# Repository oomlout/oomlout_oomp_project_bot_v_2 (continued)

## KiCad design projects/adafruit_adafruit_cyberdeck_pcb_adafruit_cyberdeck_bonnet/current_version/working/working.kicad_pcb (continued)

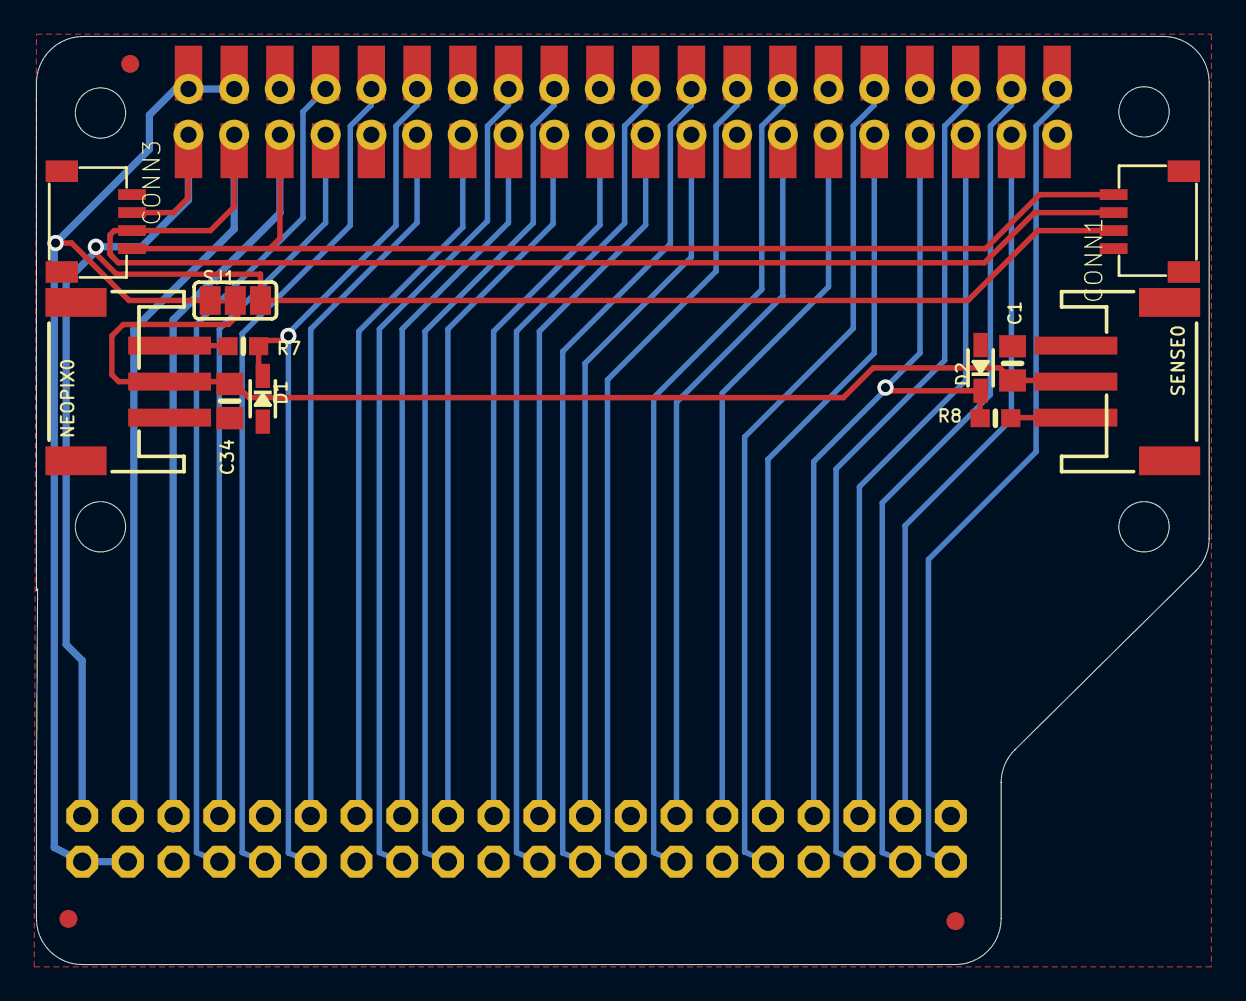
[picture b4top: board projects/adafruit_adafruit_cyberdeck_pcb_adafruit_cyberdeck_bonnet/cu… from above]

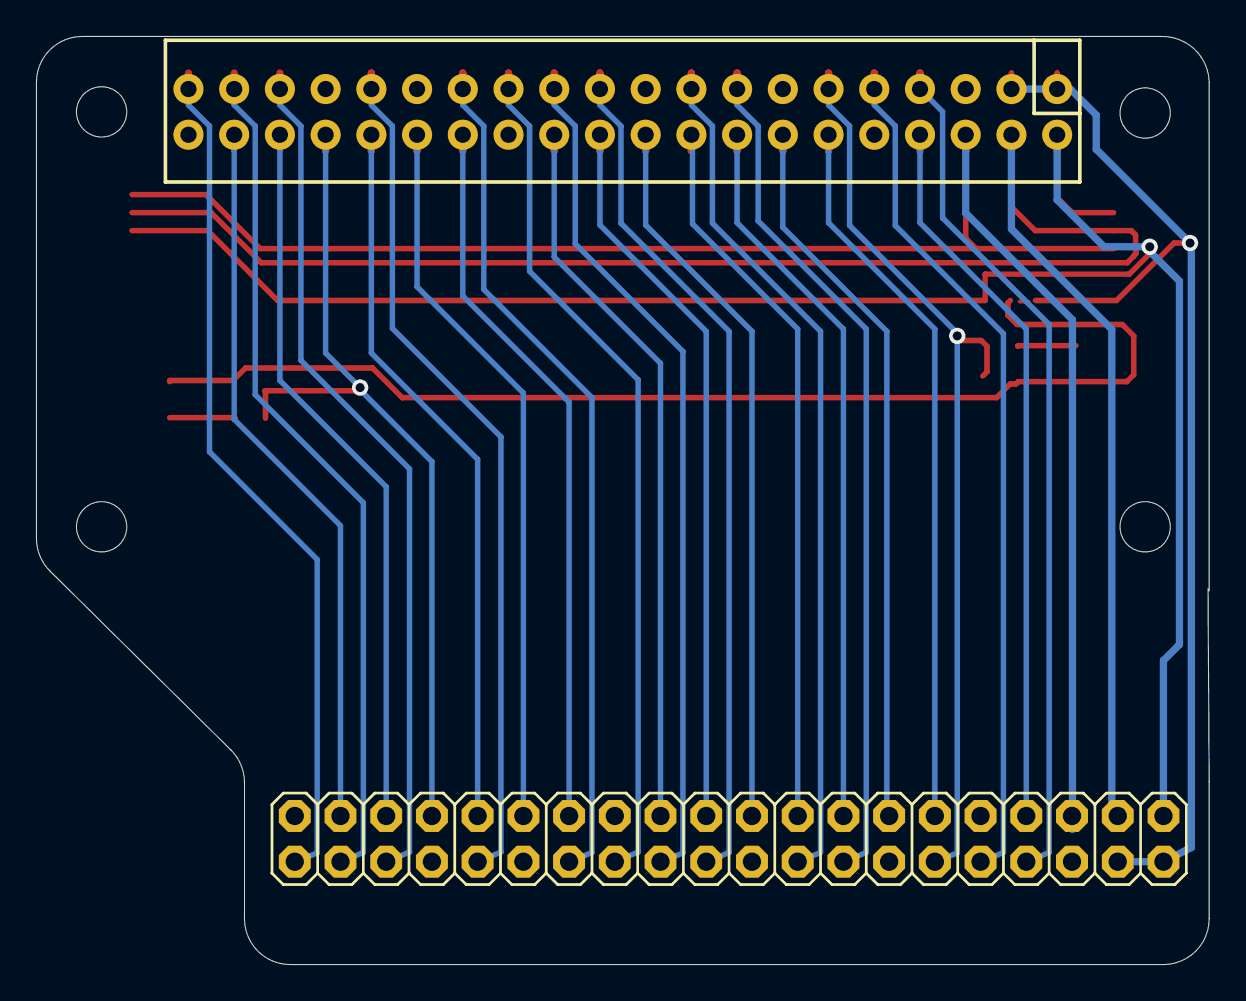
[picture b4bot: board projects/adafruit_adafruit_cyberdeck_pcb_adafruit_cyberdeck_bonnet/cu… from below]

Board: 2 copper layers, 65.2 x 51.6 mm, 22 parts (2 on the bottom side), 35 nets.

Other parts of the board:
@HOLE0, @HOLE1, @HOLE2, @HOLE3: (no value)
U$1: CYBERDECK_BONNET_BOT
U$2: CYBERDECK_BONNET_TOP

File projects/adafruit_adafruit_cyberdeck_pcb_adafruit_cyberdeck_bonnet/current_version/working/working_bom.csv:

"Id";"Designator";"Footprint";"Quantity";"Designation";"Supplier and ref";
1;"FID3,FID2,FID1";"FIDUCIAL_1MM";3;"FIDUCIAL_1MM";;;
2;"CONN3,CONN1";"JST_SH4";2;"STEMMA_I2C_QT";;;
3;"R7,R8";"0603-NO";2;"1K";;;
4;"C1,C34";"0805-NO";2;"10uF";;;
5;"@HOLE0,@HOLE2,@HOLE1,@HOLE3";"";4;"";;;
6;"NEOPIX0,SENSE0";"JSTPH3";2;"JST PH 3";;;
7;"U$2";"CYBERDECK_BONNET_TOP";1;"";;;
8;"RPI2";"RASPI_2X20_THMSMT_TOP";1;"RASPBERRYPI_BPLUS_2X20_THMSMT_TOP";;;
9;"D2,D1";"SOD-323";2;"3.6V";;;
10;"SJ1";"SOLDERJUMPER_2WAY_OPEN_NOPASTE";1;"";;;
11;"RPI1";"2X20";1;"RASPBERRYPI_BPLUS_IDC";;;
12;"U$1";"CYBERDECK_BONNET_BOT";1;"";;;

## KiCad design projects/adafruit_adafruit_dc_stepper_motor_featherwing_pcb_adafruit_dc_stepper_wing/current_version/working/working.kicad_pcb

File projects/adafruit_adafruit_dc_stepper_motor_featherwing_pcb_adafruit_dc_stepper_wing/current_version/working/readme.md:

# adafruit_dc_stepper_motor_featherwing_pcb
 
## summary 
* id: adafruit_adafruit_dc_stepper_motor_featherwing_pcb_adafruit_dc_stepper_wing
* user: adafruit
* name: adafruit_dc_stepper_motor_featherwing_pcb
* board: adafruit_dc_stepper_wing
* repo: https://github.com/adafruit/Adafruit-DC-Stepper-Motor-FeatherWing-PCB

* src_file_repo_sch: 
* src_file_repo_sch_link: https://github.com/adafruit/Adafruit-DC-Stepper-Motor-FeatherWing-PCB/tree/master/
* full details link: https://github.com/oomlout/oomlout_oomp_project_bot_v_2/tree/main/projects/adafruit_adafruit_dc_stepper_motor_featherwing_pcb_adafruit_dc_stepper_wing/current_version/working  

## schematic  
  
[schematic (pdf)](working_schematic.pdf) 

## pcb  

[board (pdf)](working.pdf)  

## working_bom
| Id | Designator | Footprint | Quantity | Designation | Supplier and ref |  | None | 
| --- | --- | --- | --- | --- | --- | --- | --- | 
| 1 | R9,R10 | RESPACK_4X0603 | 2 | 10K |  |  | [''] | 
| 2 | C2 | 0805-NO | 1 | 0.1uF |  |  | [''] | 
| 3 | U$4,U$3 | FIDUCIAL_1MM | 2 | FIDUCIAL" |  |  | [''] | 
| 4 | C6,C10 | 0805-NO | 2 | 10uF |  |  | [''] | 
| 5 | U$2 | SYMBOL_MINUS | 1 |  |  |  | [''] | 
| 6 | R4 | 0805-NO | 1 | 1K |  |  | [''] | 
| 7 | X1,X4,X6,X2 | TERMBLOCK_1X2-3.5MM | 4 |  |  |  | [''] | 
| 8 | MS1 | FEATHERWING | 1 | FEATHERWING |  |  | [''] | 
| 9 | LED1 | CHIPLED_0805_NOOUTLINE | 1 | Green |  |  | [''] | 
| 10 | SW1 | BTN_KMR2_4.6X2.8 | 1 |  |  |  | [''] | 
| 11 | MPOWER0 | 1X2-3.5MM | 1 | 1X2-3.5MM |  |  | [''] | 
| 12 | U$5 | ADAFRUIT_3.5MM | 1 |  |  |  | [''] | 
| 13 | U2 | TSSOP28 | 1 | PCA9685 |  |  | [''] | 
| 14 | Q1 | POWERDI3333 | 1 | AON7401 |  |  | [''] | 
| 15 | C5 | PANASONIC_C | 1 | 47uF+/16v |  |  | [''] | 
| 16 | JP1 | 1X12_ROUND | 1 |  |  |  | [''] | 
| 17 | IC3,IC1 | SSOP24 | 2 | TB6612FNG |  |  | [''] | 
| 18 | JP2 | 1X16_ROUND | 1 |  |  |  | [''] | 
| 19 | C4 | PANASONIC_C | 1 | 47uF/16v |  |  | [''] | 
| 20 | U$1 | SYMBOL_PLUS | 1 |  |  |  | [''] | 
| 21 | A0,A1,A4,A3,A2 | SOLDERJUMPER_REFLOW_NOPASTE | 5 |  |  |  | [''] | 
| 22 | U$6 | FEATHERLOGO | 1 |  |  |  | [''] | 
| 23 | U$8 | PCBFEAT-REV-040 | 1 |  |  |  | [''] | 

## bom_schematic
| Ref | Qnty | Value | Cmp name | Footprint | Description | Vendor | DNP | 
| --- | --- | --- | --- | --- | --- | --- | --- | 
| A0, A1, A2, A3, A4 | 5 | SOLDERJUMPERREFLOW_NOPASTE | SOLDERJUMPERREFLOW_NOPASTE | working:SOLDERJUMPER_REFLOW_NOPASTE |  |  |  | 
| C2 | 1 | 0.1uF | CAP_CERAMIC0805-NOOUTLINE | working:0805-NO |  |  |  | 
| C4 | 1 | 47uF/16v | CAP_ELECTROLYTICPANASONIC_C | working:PANASONIC_C |  |  |  | 
| C5 | 1 | 47uF+/16v | CAP_ELECTROLYTICPANASONIC_C | working:PANASONIC_C |  |  |  | 
| C6, C10 | 2 | 10uF | CAP_CERAMIC0805-NOOUTLINE | working:0805-NO |  |  |  | 
| IC1, IC3 | 2 | TB6612FNG | TB6612FNG | working:SSOP24 |  |  |  | 
| JP1 | 1 | HEADER-1X12 | HEADER-1X12 | working:1X12_ROUND |  |  |  | 
| JP2 | 1 | HEADER-1X16ROUND | HEADER-1X16ROUND | working:1X16_ROUND |  |  |  | 
| LED1 | 1 | Green | LED0805_NOOUTLINE | working:CHIPLED_0805_NOOUTLINE |  |  |  | 
| MPOWER0 | 1 | 1X2-3.5MM | 1X2-3.5MM | working:1X2-3.5MM |  |  |  | 
| MS1 | 1 | FEATHERWING | FEATHERWING | working:FEATHERWING |  |  |  | 
| Q1 | 1 | AON7401 | MOSFET-P-POWERDI3333 | working:POWERDI3333 |  |  |  | 
| R4 | 1 | 1K | RESISTOR0805_NOOUTLINE | working:0805-NO |  |  |  | 
| R9, R10 | 2 | 10K | RESISTOR_4PACK | working:RESPACK_4X0603 |  |  |  | 
| SW1 | 1 | SWITCH_TACT_SMT4.6X2.8 | SWITCH_TACT_SMT4.6X2.8 | working:BTN_KMR2_4.6X2.8 |  |  |  | 
| U2 | 1 | PCA9685 | PCA9685 | working:TSSOP28 |  |  |  | 
| U$3, U$4 | 2 | FIDUCIAL"" | FIDUCIAL{dblquote}{dblquote} | working:FIDUCIAL_1MM |  |  |  | 
| X1, X2, X4, X6 | 4 | TERMBLOCK_1X2 | TERMBLOCK_1X2 | working:TERMBLOCK_1X2-3.5MM |  |  |  |

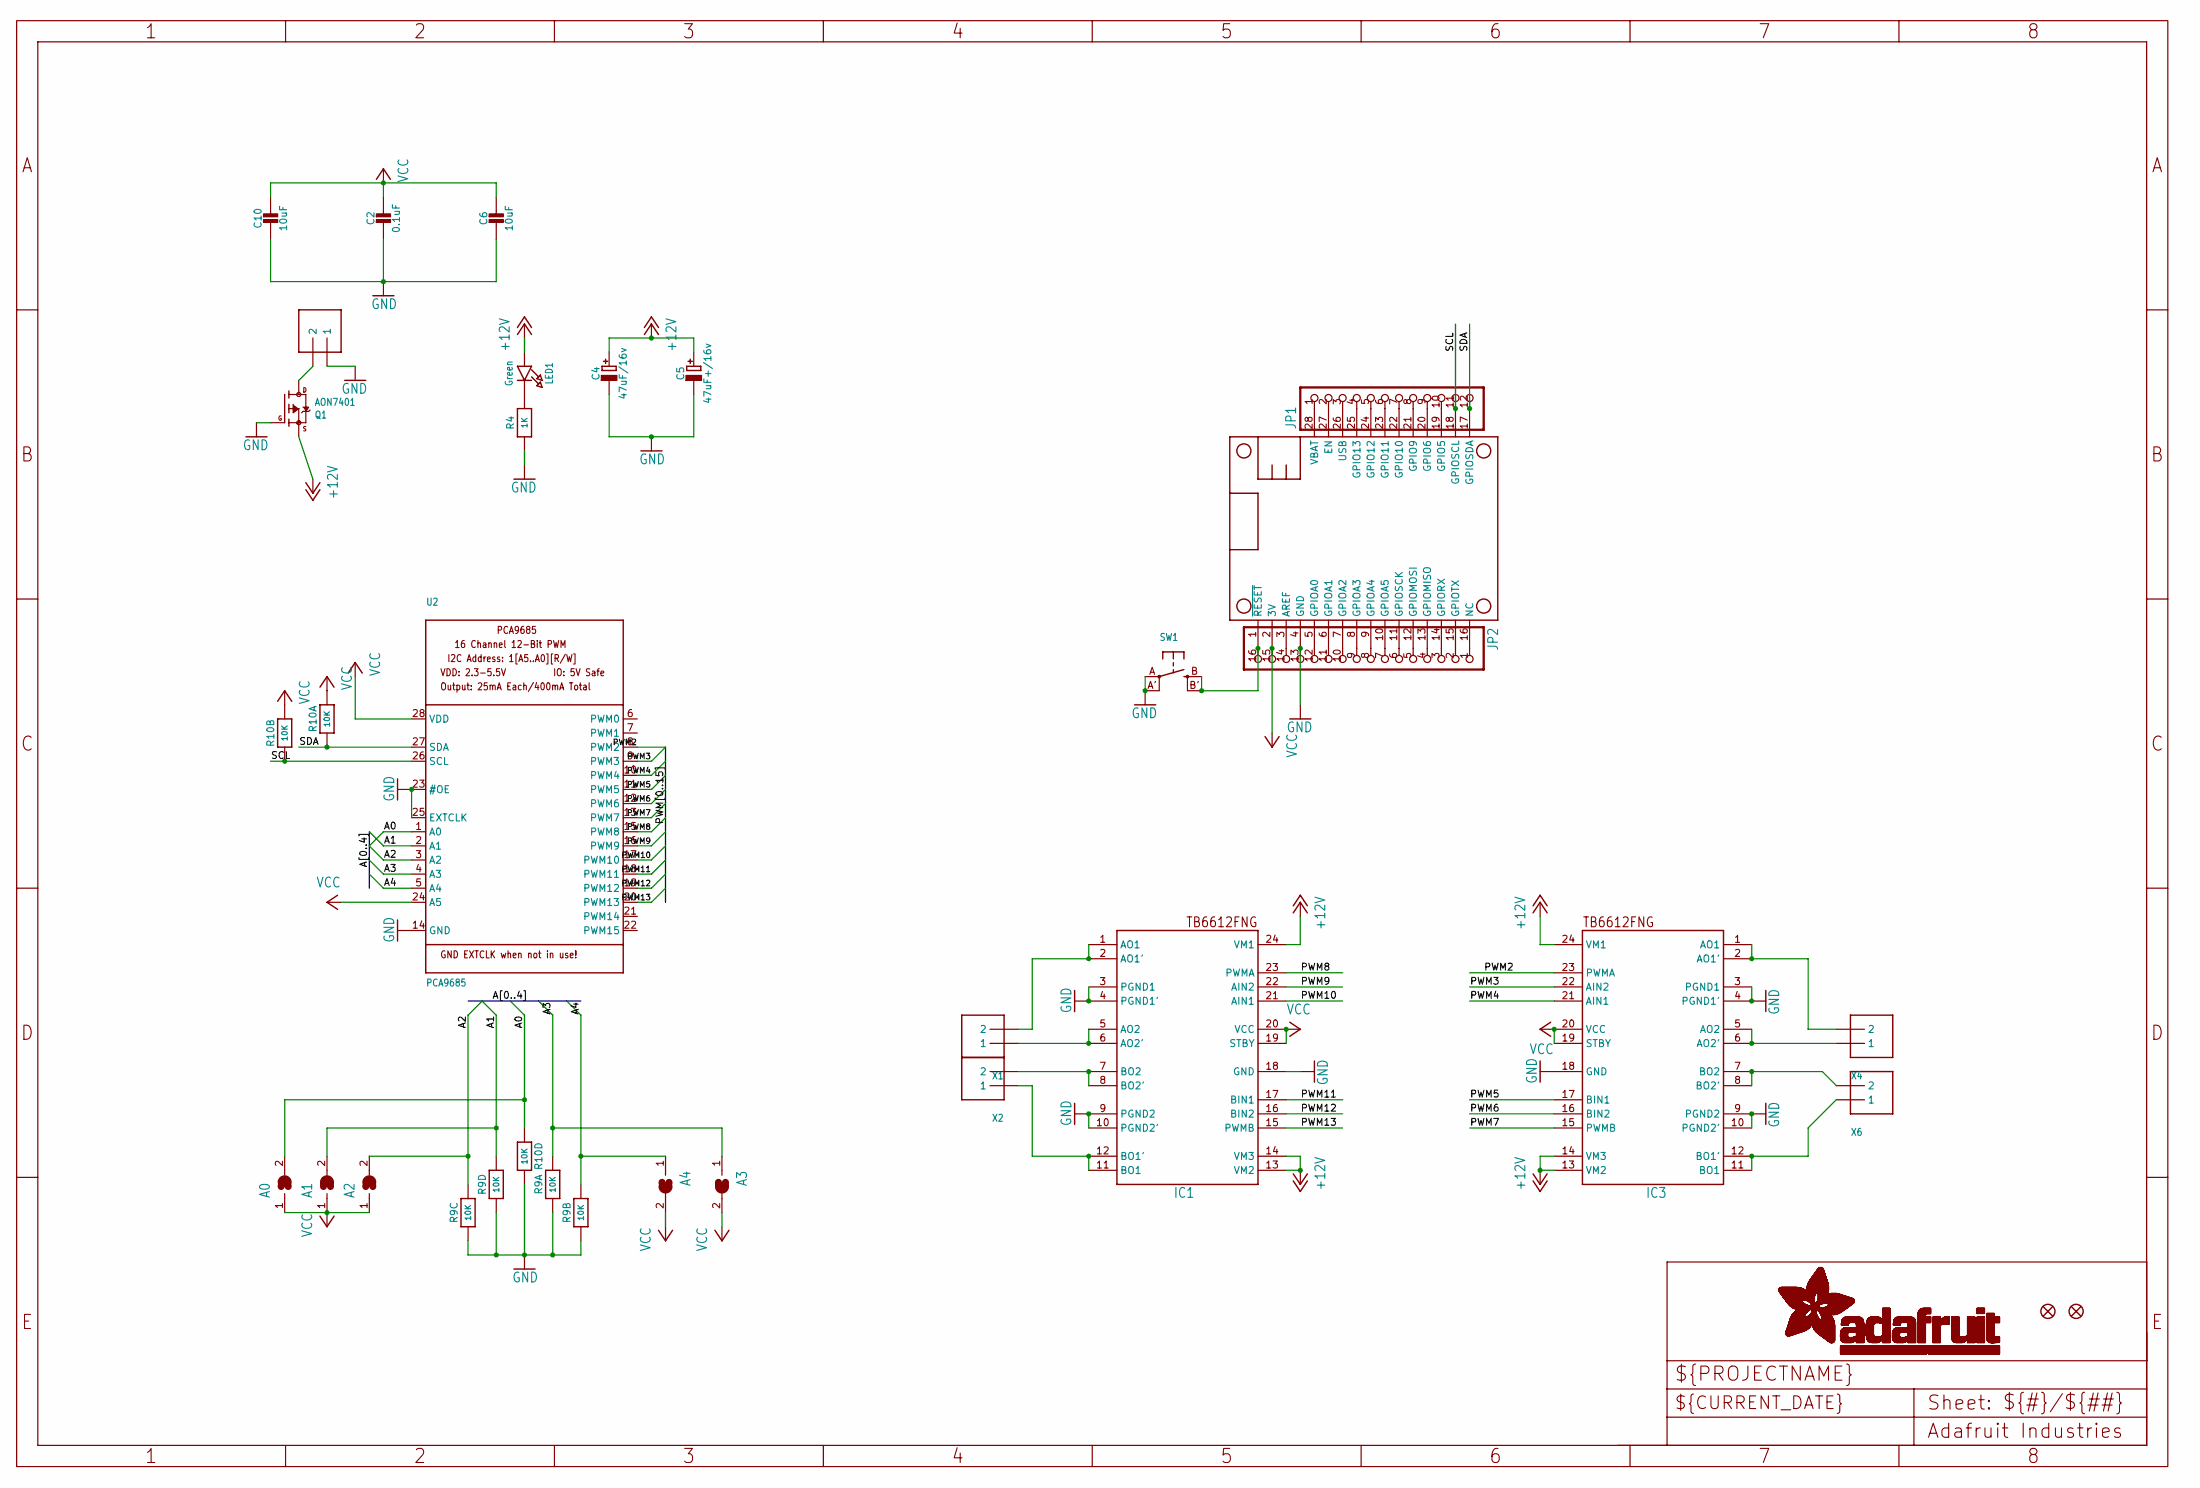
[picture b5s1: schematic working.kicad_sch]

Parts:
A0, A1, A2, A3, A4: SOLDERJUMPERREFLOW_NOPASTE; SOLDERJUMPER_REFLOW_NOPASTE
C2: 0.1uF; 0805-NO
C4: 47uF/16v; PANASONIC_C
C5: 47uF+/16v; PANASONIC_C
C6, C10: 10uF; 0805-NO
IC1, IC3: TB6612FNG; SSOP24
JP1: HEADER-1X12; 1X12_ROUND
JP2: HEADER-1X16ROUND; 1X16_ROUND
LED1: Green; CHIPLED_0805_NOOUTLINE
MPOWER0: 1X2-3.5MM
MS1: FEATHERWING
Q1: AON7401; POWERDI3333
R4: 1K; 0805-NO
R9, R10: 10K; RESPACK_4X0603
SW1: SWITCH_TACT_SMT4.6X2.8; BTN_KMR2_4.6X2.8
U2: PCA9685; TSSOP28
U$3, U$4: FIDUCIAL""; FIDUCIAL_1MM
X1, X2, X4, X6: TERMBLOCK_1X2; TERMBLOCK_1X2-3.5MM

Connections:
+12V: C4.+, C5.+, IC1.13 (VM2), IC1.14 (VM3), IC1.24 (VM1), IC3.13 (VM2), IC3.14 (VM3), IC3.24 (VM1), LED1.A, Q1.1 (S), Q1.2 (S), Q1.3 (S)
A0: A0.2, R10.4 (1), U2.1 (A0)
A1: A1.2, R9.5 (2), U2.2 (A1)
A2: A2.2, R9.6 (2), U2.3 (A2)
A3: A3.1, R9.8 (2), U2.4 (A3)
A4: A4.1, R9.7 (2), U2.5 (A4)
GND: C2.2, C4.-, C5.-, C6.2, C10.2, IC1.3 (PGND1), IC1.4 (PGND1'), IC1.9 (PGND2), IC1.10 (PGND2'), IC1.18 (GND), IC3.3 (PGND1), IC3.4 (PGND1'), IC3.9 (PGND2), IC3.10 (PGND2'), IC3.18 (GND), JP2.13, MPOWER0.1, MS1.4 (GND), Q1.4 (G), R4.1, R9.1, R9.2 (1), R9.3 (1), R9.4 (1), R10.5 (2), SW1.A, SW1.A' (P1), U2.14 (GND), U2.23 (#OE), U2.25 (EXTCLK)
unnamed: JP1.2, MS1.27 (EN)
unnamed: JP1.4, MS1.25 (GPIO13)
unnamed: MPOWER0.2, Q1.5678 (D)
unnamed: IC1.1 (AO1), IC1.2 (AO1'), X1.2
unnamed: JP1.5, MS1.24 (GPIO12)
unnamed: IC1.5 (AO2), IC1.6 (AO2'), X1.1
unnamed: IC1.7 (BO2), IC1.8 (BO2'), X2.2
unnamed: JP1.6, MS1.23 (GPIO11)
unnamed: IC1.11 (BO1), IC1.12 (BO1'), X2.1
unnamed: JP1.7, MS1.22 (GPIO10)
unnamed: JP1.8, MS1.21 (GPIO9)
unnamed: IC3.1 (AO1), IC3.2 (AO1'), X4.2
unnamed: JP1.9, MS1.20 (GPIO6)
unnamed: IC3.5 (AO2), IC3.6 (AO2'), X4.1
unnamed: IC3.7 (BO2), IC3.8 (BO2'), X6.2
unnamed: JP1.10, MS1.19 (GPIO5)
unnamed: IC3.11 (BO1), IC3.12 (BO1'), X6.1
unnamed: JP2.1, MS1.16 (NC)
unnamed: JP2.2, MS1.15 (GPIOTX)
unnamed: JP2.3, MS1.14 (GPIORX)
unnamed: JP2.4, MS1.13 (GPIOMISO)
unnamed: JP2.5, MS1.12 (GPIOMOSI)
unnamed: JP2.6, MS1.11 (GPIOSCK)
unnamed: JP2.7, MS1.10 (GPIOA5)
unnamed: JP2.8, MS1.9 (GPIOA4)
unnamed: JP2.9, MS1.8 (GPIOA3)
unnamed: JP2.10, MS1.7 (GPIOA2)
unnamed: JP2.11, MS1.6 (GPIOA1)
unnamed: JP2.12, MS1.5 (GPIOA0)
unnamed: JP2.14, MS1.3 (AREF)
unnamed: JP2.16, MS1.1 (~RESET), SW1.B (S), SW1.B' (S1)
unnamed: LED1.C, R4.2
PWM2: IC3.23 (PWMA), U2.8 (PWM2)
PWM3: IC3.22 (AIN2), U2.9 (PWM3)
PWM4: IC3.21 (AIN1), U2.10 (PWM4)
PWM5: IC3.17 (BIN1), U2.11 (PWM5)
PWM6: IC3.16 (BIN2), U2.12 (PWM6)
PWM7: IC3.15 (PWMB), U2.13 (PWM7)
PWM8: IC1.23 (PWMA), U2.15 (PWM8)
PWM9: IC1.22 (AIN2), U2.16 (PWM9)
PWM10: IC1.21 (AIN1), U2.17 (PWM10)
PWM11: IC1.17 (BIN1), U2.18 (PWM11)
PWM12: IC1.16 (BIN2), U2.19 (PWM12)
PWM13: IC1.15 (PWMB), U2.20 (PWM13)
SCL: JP1.11, MS1.18 (GPIOSCL), R10.2 (1), U2.26 (SCL)
SDA: JP1.12, MS1.17 (GPIOSDA), R10.1, U2.27 (SDA)
USB: JP1.3, MS1.26 (USB)
VBAT: JP1.1, MS1.28 (VBAT)
VCC: A0.1, A1.1, A2.1, A3.2, A4.2, C2.1, C6.1, C10.1, IC1.19 (STBY), IC1.20 (VCC), IC3.19 (STBY), IC3.20 (VCC), JP2.15, MS1.2 (3V), R10.7 (2), R10.8 (2), U2.24 (A5), U2.28 (VDD)

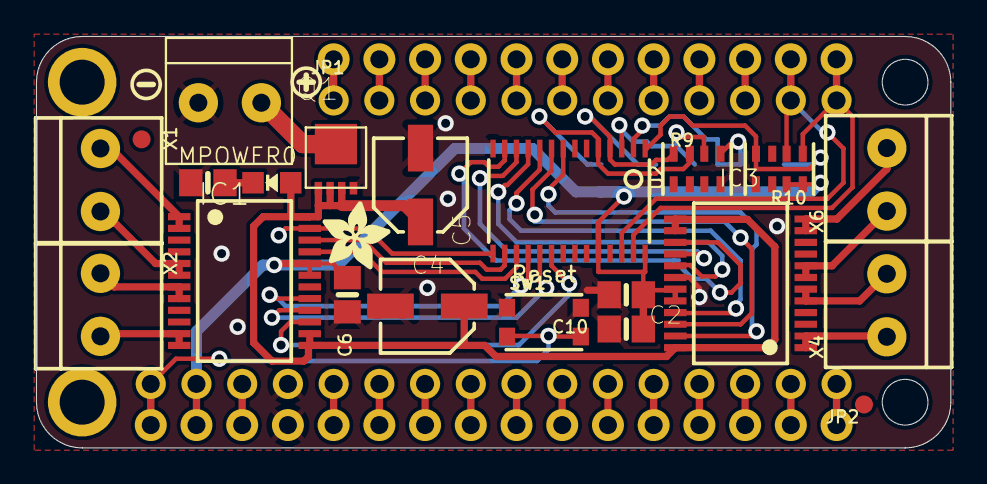
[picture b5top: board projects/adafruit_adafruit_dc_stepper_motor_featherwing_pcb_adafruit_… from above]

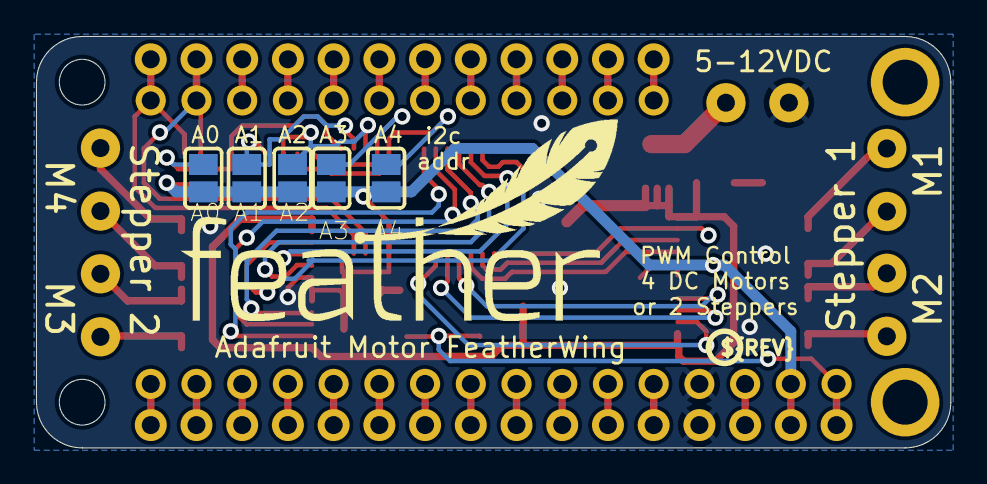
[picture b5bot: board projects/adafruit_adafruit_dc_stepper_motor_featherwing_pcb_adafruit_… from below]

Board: 16 copper layers, 50.8 x 22.9 mm, 34 parts (7 on the bottom side), 56 nets.

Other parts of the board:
U$1: SYMBOL_PLUS
U$2: SYMBOL_MINUS
U$5: ADAFRUIT_3.5MM
U$6: FEATHERLOGO
U$8: PCBFEAT-REV-040

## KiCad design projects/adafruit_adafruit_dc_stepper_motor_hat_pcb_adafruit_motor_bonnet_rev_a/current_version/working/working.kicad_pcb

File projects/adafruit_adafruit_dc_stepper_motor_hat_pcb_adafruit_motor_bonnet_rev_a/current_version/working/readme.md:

# adafruit_dc_stepper_motor_hat_pcb
 
## summary 
* id: adafruit_adafruit_dc_stepper_motor_hat_pcb_adafruit_motor_bonnet_rev_a
* user: adafruit
* name: adafruit_dc_stepper_motor_hat_pcb
* board: adafruit_motor_bonnet_rev_a
* repo: https://github.com/adafruit/Adafruit-DC-Stepper-Motor-HAT-PCB

* src_file_repo_sch: 
* src_file_repo_sch_link: https://github.com/adafruit/Adafruit-DC-Stepper-Motor-HAT-PCB/tree/master/
* full details link: https://github.com/oomlout/oomlout_oomp_project_bot_v_2/tree/main/projects/adafruit_adafruit_dc_stepper_motor_hat_pcb_adafruit_motor_bonnet_rev_a/current_version/working  

## schematic  
  
[schematic (pdf)](working_schematic.pdf) 

## pcb  

[board (pdf)](working.pdf)  

## working_bom
| Id | Designator | Footprint | Quantity | Designation | Supplier and ref |  | None | 
| --- | --- | --- | --- | --- | --- | --- | --- | 
| 1 | MPOWER0 | 1X2-3.5MM | 1 | 1X2-3.5MM |  |  | [''] | 
| 2 | C6,C10 | 0805-NO | 2 | 10uF |  |  | [''] | 
| 3 | Q1 | D-PAK_TO252AA | 1 | AOD417 |  |  | [''] | 
| 4 | U2 | TSSOP28 | 1 | PCA9685 |  |  | [''] | 
| 5 | RPI1 | PI_BONNET_THMSMT | 1 | RASPBERRYPI_BPLUS_BONNET_THMSMT |  |  | [''] | 
| 6 | C5 | PANASONIC_C | 1 | 47uF+/16v |  |  | [''] | 
| 7 | R2 | 0603-NO | 1 | 10K |  |  | [''] | 
| 8 | R7 | 0603-NO | 1 | 1K |  |  | [''] | 
| 9 | C3,C1 | 0603-NO | 2 | 0.1uF |  |  | [''] | 
| 10 | IC1,IC3 | SSOP24 | 2 | TB6612FNG |  |  | [''] | 
| 11 | FID2,FID1,FID3 | FIDUCIAL_1MM | 3 | FIDUCIAL_1MM |  |  | [''] | 
| 12 | LED1 | CHIPLED_0805_NOOUTLINE | 1 | Green |  |  | [''] | 
| 13 | J1,J3 | 1X05-3.5MM | 2 | 1X5 |  |  | [''] | 
| 14 | U$6 | PCBFEAT-REV-040 | 1 |  |  |  | [''] | 
| 15 | JP1 | 1X04_ROUND | 1 |  |  |  | [''] | 
| 16 | C4 | PANASONIC_C | 1 | 47uF/16v |  |  | [''] | 
| 17 | R1 | RESPACK_4X0603 | 1 | 10K |  |  | [''] | 
| 18 | CONN1 | 1X25_ROUND_70MIL | 1 | HEADER-1X25 |  |  | [''] | 
| 19 | U$51 | ADAFRUIT_5MM | 1 |  |  |  | [''] | 
| 20 | A1,A2,A3,A4,A0 | SOLDERJUMPER_REFLOW_NOPASTE | 5 |  |  |  | [''] | 
| 21 | U$8 | ADAFRUIT_TEXT_20MM | 1 |  |  |  | [''] | 

## bom_schematic
| Ref | Qnty | Value | Cmp name | Footprint | Description | Vendor | DNP | 
| --- | --- | --- | --- | --- | --- | --- | --- | 
| A0, A1, A2, A3, A4 | 5 | SOLDERJUMPERREFLOW_NOPASTE | SOLDERJUMPERREFLOW_NOPASTE | working:SOLDERJUMPER_REFLOW_NOPASTE |  |  |  | 
| C1, C3 | 2 | 0.1uF | CAP_CERAMIC0603_NO | working:0603-NO |  |  |  | 
| C4 | 1 | 47uF/16v | CAP_ELECTROLYTICPANASONIC_C | working:PANASONIC_C |  |  |  | 
| C5 | 1 | 47uF+/16v | CAP_ELECTROLYTICPANASONIC_C | working:PANASONIC_C |  |  |  | 
| C6, C10 | 2 | 10uF | CAP_CERAMIC0805-NOOUTLINE | working:0805-NO |  |  |  | 
| CONN1 | 1 | HEADER-1X25 | HEADER-1X25 | working:1X25_ROUND_70MIL |  |  |  | 
| FID1, FID2, FID3 | 3 | FIDUCIAL_1MM | FIDUCIAL_1MM | working:FIDUCIAL_1MM |  |  |  | 
| IC1, IC3 | 2 | TB6612FNG | TB6612FNG | working:SSOP24 |  |  |  | 
| J1, J3 | 2 | 1X5 | 1X5 | working:1X05-3.5MM |  |  |  | 
| JP1 | 1 | HEADER-1X4ROUND | HEADER-1X4ROUND | working:1X04_ROUND |  |  |  | 
| LED1 | 1 | Green | LED0805_NOOUTLINE | working:CHIPLED_0805_NOOUTLINE |  |  |  | 
| MPOWER0 | 1 | 1X2-3.5MM | 1X2-3.5MM | working:1X2-3.5MM |  |  |  | 
| Q1 | 1 | IRF?5305R | IRF?5305R | working:D-PAK_TO252AA |  |  |  | 
| R1 | 1 | 10K | RESISTOR_4PACK | working:RESPACK_4X0603 |  |  |  | 
| R2 | 1 | 10K | RESISTOR_0603_NOOUT | working:0603-NO |  |  |  | 
| R7 | 1 | 1K | RESISTOR_0603_NOOUT | working:0603-NO |  |  |  | 
| RPI1 | 1 | RASPBERRYPI_BPLUS_BONNET_THMSMT | RASPBERRYPI_BPLUS_BONNET_THMSMT | working:PI_BONNET_THMSMT |  |  |  | 
| U2 | 1 | PCA9685 | PCA9685 | working:TSSOP28 |  |  |  |

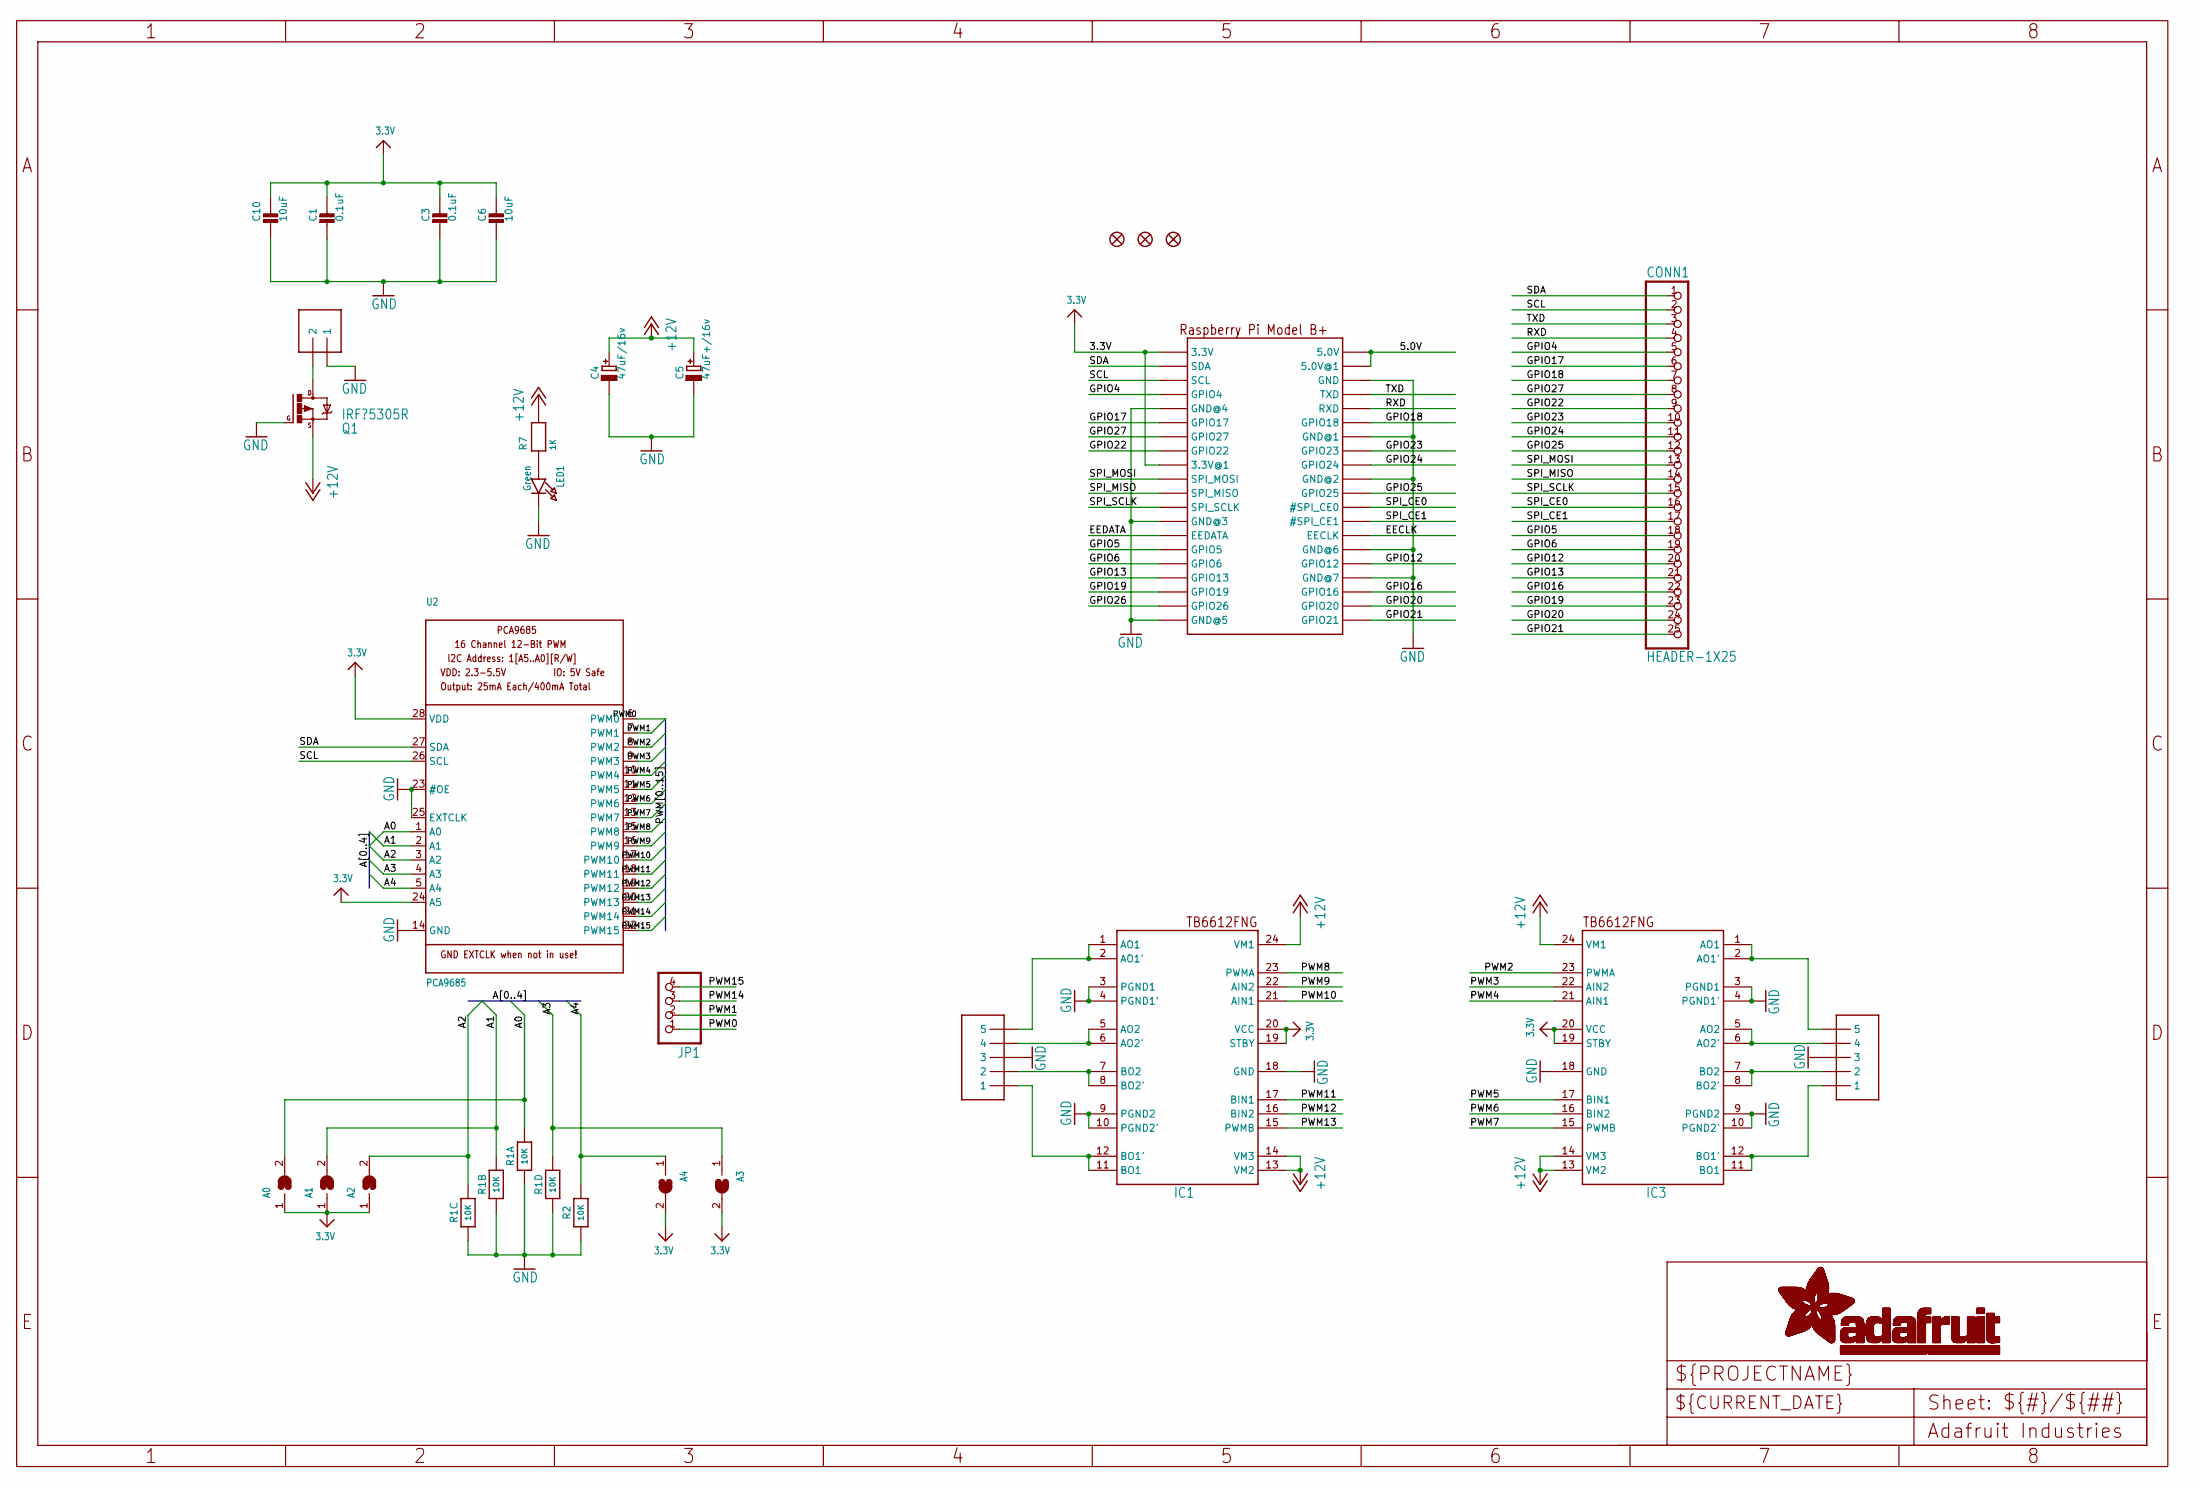
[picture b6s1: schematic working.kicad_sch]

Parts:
A0, A1, A2, A3, A4: SOLDERJUMPERREFLOW_NOPASTE; SOLDERJUMPER_REFLOW_NOPASTE
C1, C3: 0.1uF; 0603-NO
C4: 47uF/16v; PANASONIC_C
C5: 47uF+/16v; PANASONIC_C
C6, C10: 10uF; 0805-NO
CONN1: HEADER-1X25; 1X25_ROUND_70MIL
FID1, FID2, FID3: FIDUCIAL_1MM
IC1, IC3: TB6612FNG; SSOP24
J1, J3: 1X5; 1X05-3.5MM
JP1: HEADER-1X4ROUND; 1X04_ROUND
LED1: Green; CHIPLED_0805_NOOUTLINE
MPOWER0: 1X2-3.5MM
Q1: IRF?5305R; D-PAK_TO252AA
R1: 10K; RESPACK_4X0603
R2: 10K; 0603-NO
R7: 1K; 0603-NO
RPI1: RASPBERRYPI_BPLUS_BONNET_THMSMT; PI_BONNET_THMSMT
U2: PCA9685; TSSOP28

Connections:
3.3V: A0.1, A1.1, A2.1, A3.2, A4.2, C1.1, C3.1, C6.1, C10.1, IC1.19 (STBY), IC1.20 (VCC), IC3.19 (STBY), IC3.20 (VCC), RPI1.1 (3.3V), RPI1.17 (3.3V@1), RPI1.S1 (3.3V), RPI1.S17 (3.3V@1), U2.24 (A5), U2.28 (VDD)
5.0V: RPI1.2 (5.0V), RPI1.4 (5.0V@1), RPI1.S2 (5.0V), RPI1.S4 (5.0V@1)
+12V: C4.+, C5.+, IC1.13 (VM2), IC1.14 (VM3), IC1.24 (VM1), IC3.13 (VM2), IC3.14 (VM3), IC3.24 (VM1), Q1.3 (S), R7.2
A0: A0.2, R1.8 (2), U2.1 (A0)
A1: A1.2, R1.7 (2), U2.2 (A1)
A2: A2.2, R1.6 (2), U2.3 (A2)
A3: A3.1, R1.5 (2), U2.4 (A3)
A4: A4.1, R2.2, U2.5 (A4)
EECLK: RPI1.28 (EECLK), RPI1.S28 (EECLK)
EEDATA: RPI1.27 (EEDATA), RPI1.S27 (EEDATA)
GND: C1.2, C3.2, C4.-, C5.-, C6.2, C10.2, IC1.3 (PGND1), IC1.4 (PGND1'), IC1.9 (PGND2), IC1.10 (PGND2'), IC1.18 (GND), IC3.3 (PGND1), IC3.4 (PGND1'), IC3.9 (PGND2), IC3.10 (PGND2'), IC3.18 (GND), J1.3, J3.3, LED1.C, MPOWER0.1, Q1.1 (G), R1.1, R1.2 (1), R1.3 (1), R1.4 (1), R2.1, RPI1.6 (GND), RPI1.9 (GND@4), RPI1.14 (GND@1), RPI1.20 (GND@2), RPI1.25 (GND@3), RPI1.30 (GND@6), RPI1.34 (GND@7), RPI1.39 (GND@5), RPI1.S6 (GND), RPI1.S9 (GND@4), RPI1.S14 (GND@1), RPI1.S20 (GND@2), RPI1.S25 (GND@3), RPI1.S30 (GND@6), RPI1.S34 (GND@7), RPI1.S39 (GND@5), U2.14 (GND), U2.23 (#OE), U2.25 (EXTCLK)
GPIO4: CONN1.5, RPI1.7 (GPIO4), RPI1.S7 (GPIO4)
GPIO5: CONN1.18, RPI1.29 (GPIO5), RPI1.S29 (GPIO5)
GPIO6: CONN1.19, RPI1.31 (GPIO6), RPI1.S31 (GPIO6)
GPIO12: CONN1.20, RPI1.32 (GPIO12), RPI1.S32 (GPIO12)
GPIO13: CONN1.21, RPI1.33 (GPIO13), RPI1.S33 (GPIO13)
GPIO16: CONN1.22, RPI1.36 (GPIO16), RPI1.S36 (GPIO16)
GPIO17: CONN1.6, RPI1.11 (GPIO17), RPI1.S11 (GPIO17)
GPIO18: CONN1.7, RPI1.12 (GPIO18), RPI1.S12 (GPIO18)
GPIO19: CONN1.23, RPI1.35 (GPIO19), RPI1.S35 (GPIO19)
GPIO20: CONN1.24, RPI1.38 (GPIO20), RPI1.S38 (GPIO20)
GPIO21: CONN1.25, RPI1.40 (GPIO21), RPI1.S40 (GPIO21)
GPIO22: CONN1.9, RPI1.15 (GPIO22), RPI1.S15 (GPIO22)
GPIO23: CONN1.10, RPI1.16 (GPIO23), RPI1.S16 (GPIO23)
GPIO24: CONN1.11, RPI1.18 (GPIO24), RPI1.S18 (GPIO24)
GPIO25: CONN1.12, RPI1.22 (GPIO25), RPI1.S22 (GPIO25)
GPIO26: RPI1.37 (GPIO26), RPI1.S37 (GPIO26)
GPIO27: CONN1.8, RPI1.13 (GPIO27), RPI1.S13 (GPIO27)
M1A: IC1.1 (AO1), IC1.2 (AO1'), J1.5
M1B: IC1.5 (AO2), IC1.6 (AO2'), J1.4
M2A: IC1.11 (BO1), IC1.12 (BO1'), J1.1
M2B: IC1.7 (BO2), IC1.8 (BO2'), J1.2
M3A: IC3.1 (AO1), IC3.2 (AO1'), J3.5
M3B: IC3.5 (AO2), IC3.6 (AO2'), J3.4
M4A: IC3.11 (BO1), IC3.12 (BO1'), J3.1
M4B: IC3.7 (BO2), IC3.8 (BO2'), J3.2
unnamed: LED1.A, R7.1
PWM0: JP1.1, U2.6 (PWM0)
PWM1: JP1.2, U2.7 (PWM1)
PWM2: IC3.23 (PWMA), U2.8 (PWM2)
PWM3: IC3.22 (AIN2), U2.9 (PWM3)
PWM4: IC3.21 (AIN1), U2.10 (PWM4)
PWM5: IC3.17 (BIN1), U2.11 (PWM5)
PWM6: IC3.16 (BIN2), U2.12 (PWM6)
PWM7: IC3.15 (PWMB), U2.13 (PWM7)
PWM8: IC1.23 (PWMA), U2.15 (PWM8)
PWM9: IC1.22 (AIN2), U2.16 (PWM9)
PWM10: IC1.21 (AIN1), U2.17 (PWM10)
PWM11: IC1.17 (BIN1), U2.18 (PWM11)
PWM12: IC1.16 (BIN2), U2.19 (PWM12)
PWM13: IC1.15 (PWMB), U2.20 (PWM13)
PWM14: JP1.3, U2.21 (PWM14)
PWM15: JP1.4, U2.22 (PWM15)
RXD: CONN1.4, RPI1.10 (RXD), RPI1.S10 (RXD)
SCL: CONN1.2, RPI1.5 (SCL), RPI1.S5 (SCL), U2.26 (SCL)
SDA: CONN1.1, RPI1.3 (SDA), RPI1.S3 (SDA), U2.27 (SDA)
SPI_CE0: CONN1.16, RPI1.24 (#SPI_CE0), RPI1.S24 (#SPI_CE0)
SPI_CE1: CONN1.17, RPI1.26 (#SPI_CE1), RPI1.S26 (#SPI_CE1)
SPI_MISO: CONN1.14, RPI1.21 (SPI_MISO), RPI1.S21 (SPI_MISO)
SPI_MOSI: CONN1.13, RPI1.19 (SPI_MOSI), RPI1.S19 (SPI_MOSI)
SPI_SCLK: CONN1.15, RPI1.23 (SPI_SCLK), RPI1.S23 (SPI_SCLK)
TXD: CONN1.3, RPI1.8 (TXD), RPI1.S8 (TXD)
VMOTOR: MPOWER0.2, Q1.4 (D)

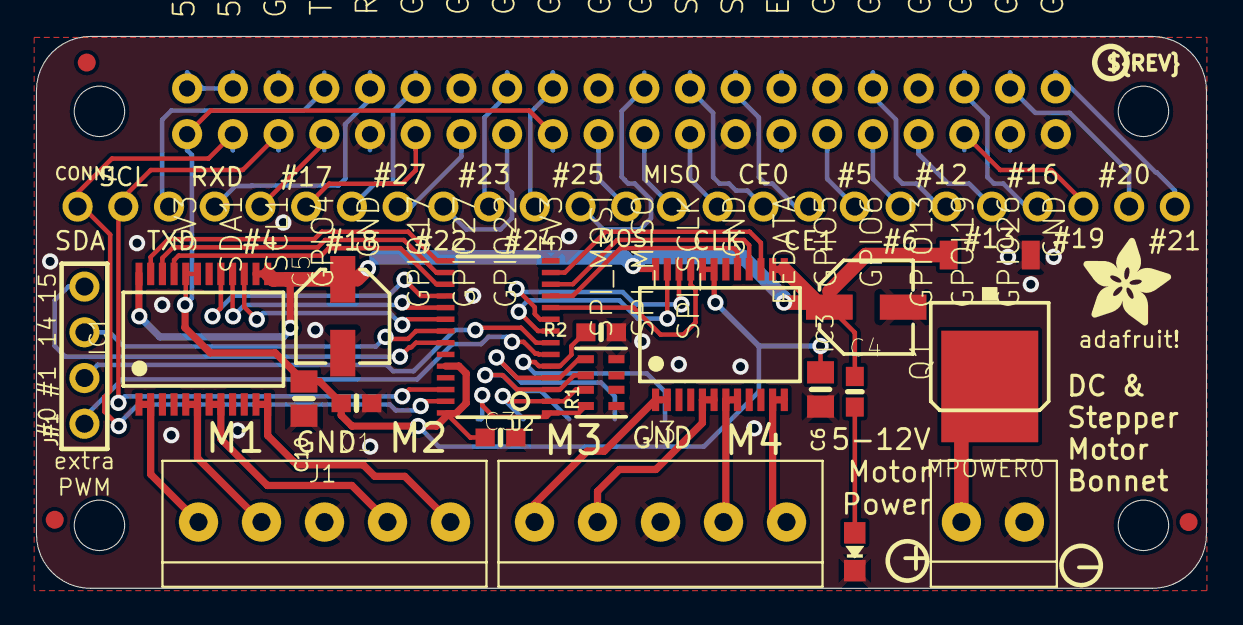
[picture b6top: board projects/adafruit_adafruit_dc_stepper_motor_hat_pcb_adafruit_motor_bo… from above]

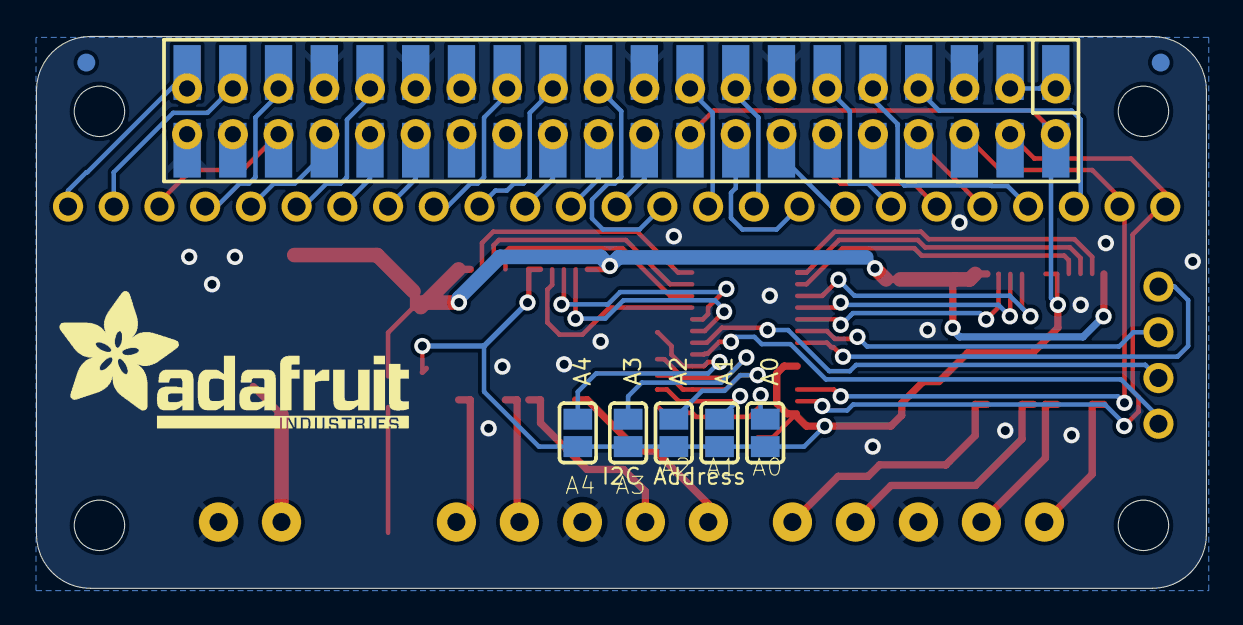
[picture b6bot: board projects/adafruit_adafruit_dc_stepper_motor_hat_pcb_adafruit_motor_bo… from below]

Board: 2 copper layers, 65.0 x 30.7 mm, 31 parts (6 on the bottom side), 63 nets.

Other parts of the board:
U$6: PCBFEAT-REV-040
U$8: ADAFRUIT_TEXT_20MM
U$51: ADAFRUIT_5MM
